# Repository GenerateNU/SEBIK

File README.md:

# SEBIK
The software portion of the safety subsystem will mostly deal with less critical errors as it is assumed that there is still communication between the microcontroller and its peripherals. The main software safety feature exists in the heating state. As the code runs through the state machine every 10 milliseconds or so, it checks if we must switch the band heater on or off based on two conditions. Are we at or above our optimal plastic melting temperature and have we heated at that optimal temperature for the full duration required to melt the pellets. 

Since, this is a software safety feature, there is a chance that it can fail in case we get stuck in some infinite loop due to an edge case or our microcontroller becomes unresponsive. A watchdog timer was used in the main state machine so it could reset the microcontroller in case any of these happened.

The band heater is allowed to operate for 4 minutes as some time is needed to reach the 165°C required to melt the PP. and 3.5 minutes is required for the band heater to completely melt all the PP within the barrel before moving to the next state. 

To do so, the code employs a timer that is initialized at the beginning of the Heating State. This conditional allows the heater to count the amount of time the band heater has been operating at the proper temperature. A watchdog timer will only run when the heater is at an optimal state and count until it reaches 4 minutes of heating time. In real time, this causes the process to run for longer than 4 minutes, however, this is necessary to ensure all the PP is melted.

## Directory Structure:
```
.
|
|───production  # contains files needed for final prototype
|   |
|   |───sebik-eCAD    # contains the KiCAD project
|   └───sebik-src     # contains the code needed for deployment
|
|───testing     # contains files relevant to testing components
|
└───README.md   # this file!
```

## Practice Good Git Hygiene!
1. Only commit files you intended to change
2. Create branches for each feature, and larger branches for each development effort (i.e. ```develop/*```)
3. Check your branch before starting work
4. Pull frequently to avoid conflicts
5. Make Pull Requests when you are ready to merge into a larger branch

## Git Resources

* [Setting up Git](https://fanatical-colossus-434.notion.site/Git-Installation-and-Setup-d07b7d1ab5544424876f9fd3b4a0b312)
* [Intro to Git Crash Course](https://fanatical-colossus-434.notion.site/Crash-Course-Intro-to-Git-809641611da9478b8f9cca8fd97e49fe)

## EE Resources

* [Intro to KiCAD](https://fanatical-colossus-434.notion.site/EE-Crashcourse-Using-Kicad-To-Design-Schematics-8c7091b07237425bae66616ad1f77371)
* [EE Crash Course](https://fanatical-colossus-434.notion.site/EE-Crash-Course-Hardware-2023-c0c7cd5b55cf401e87f8b6c2c8c84336)

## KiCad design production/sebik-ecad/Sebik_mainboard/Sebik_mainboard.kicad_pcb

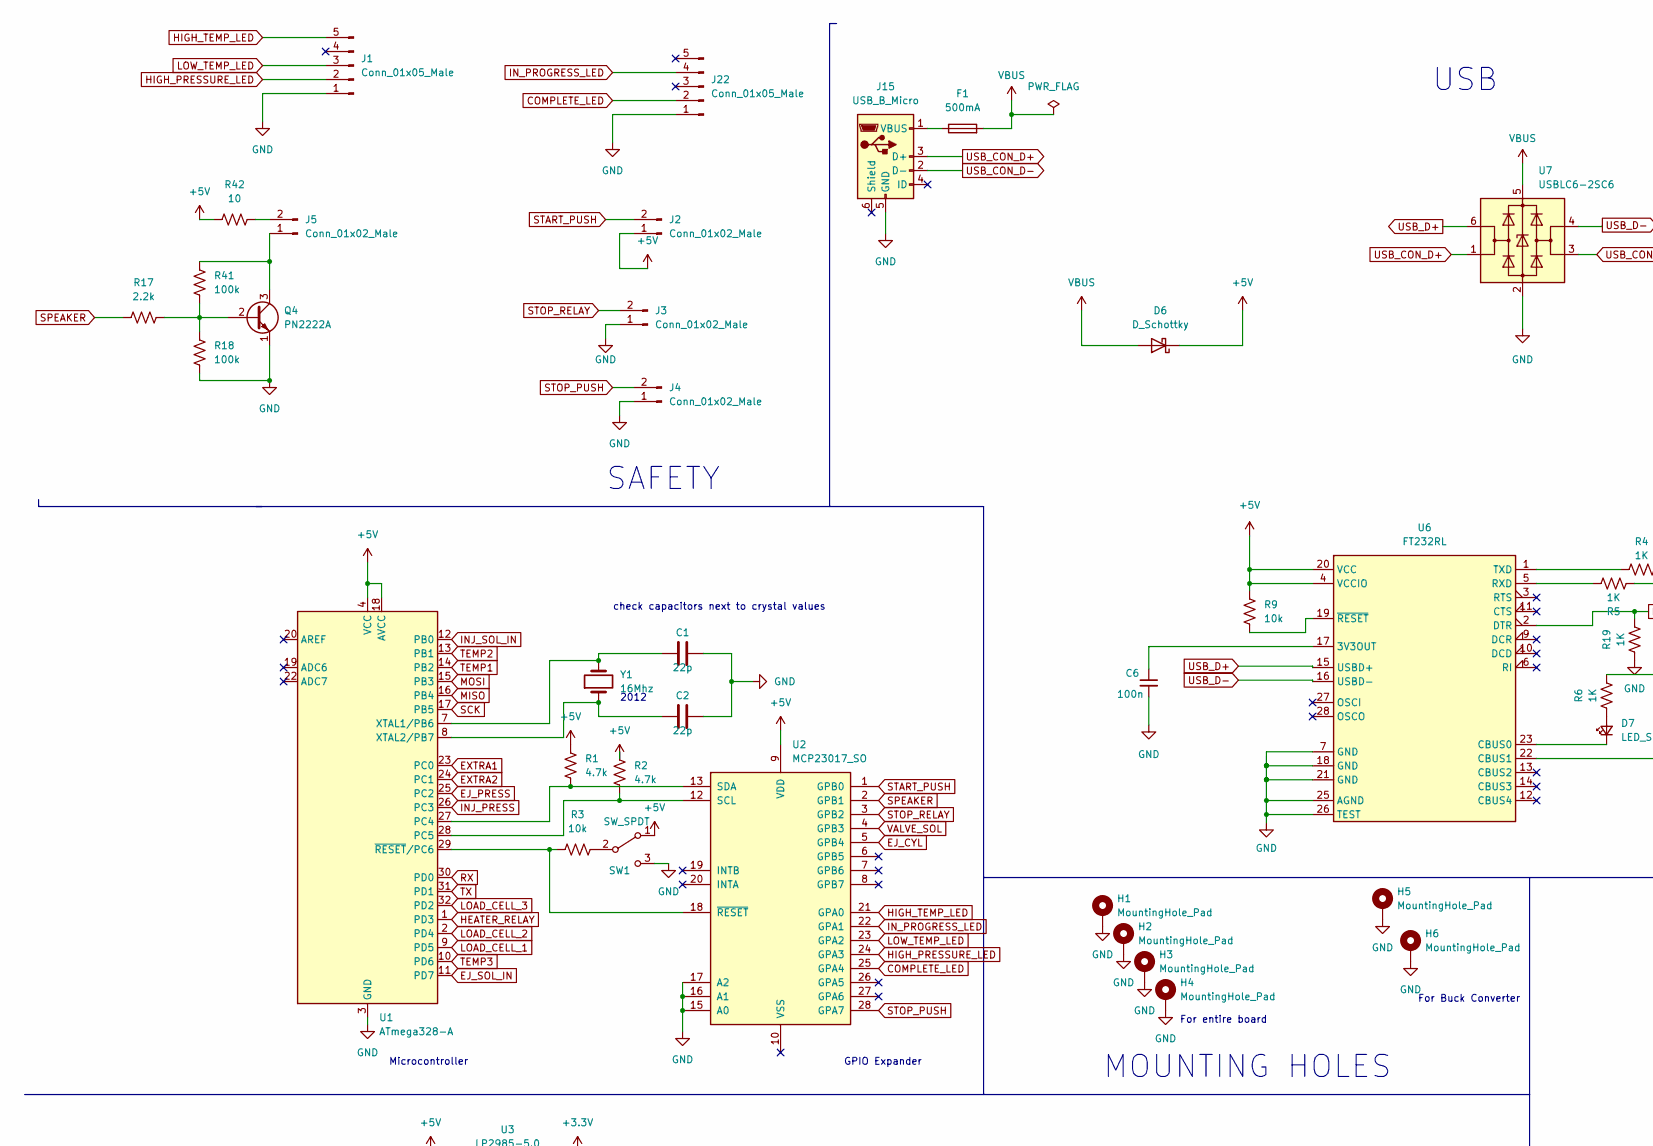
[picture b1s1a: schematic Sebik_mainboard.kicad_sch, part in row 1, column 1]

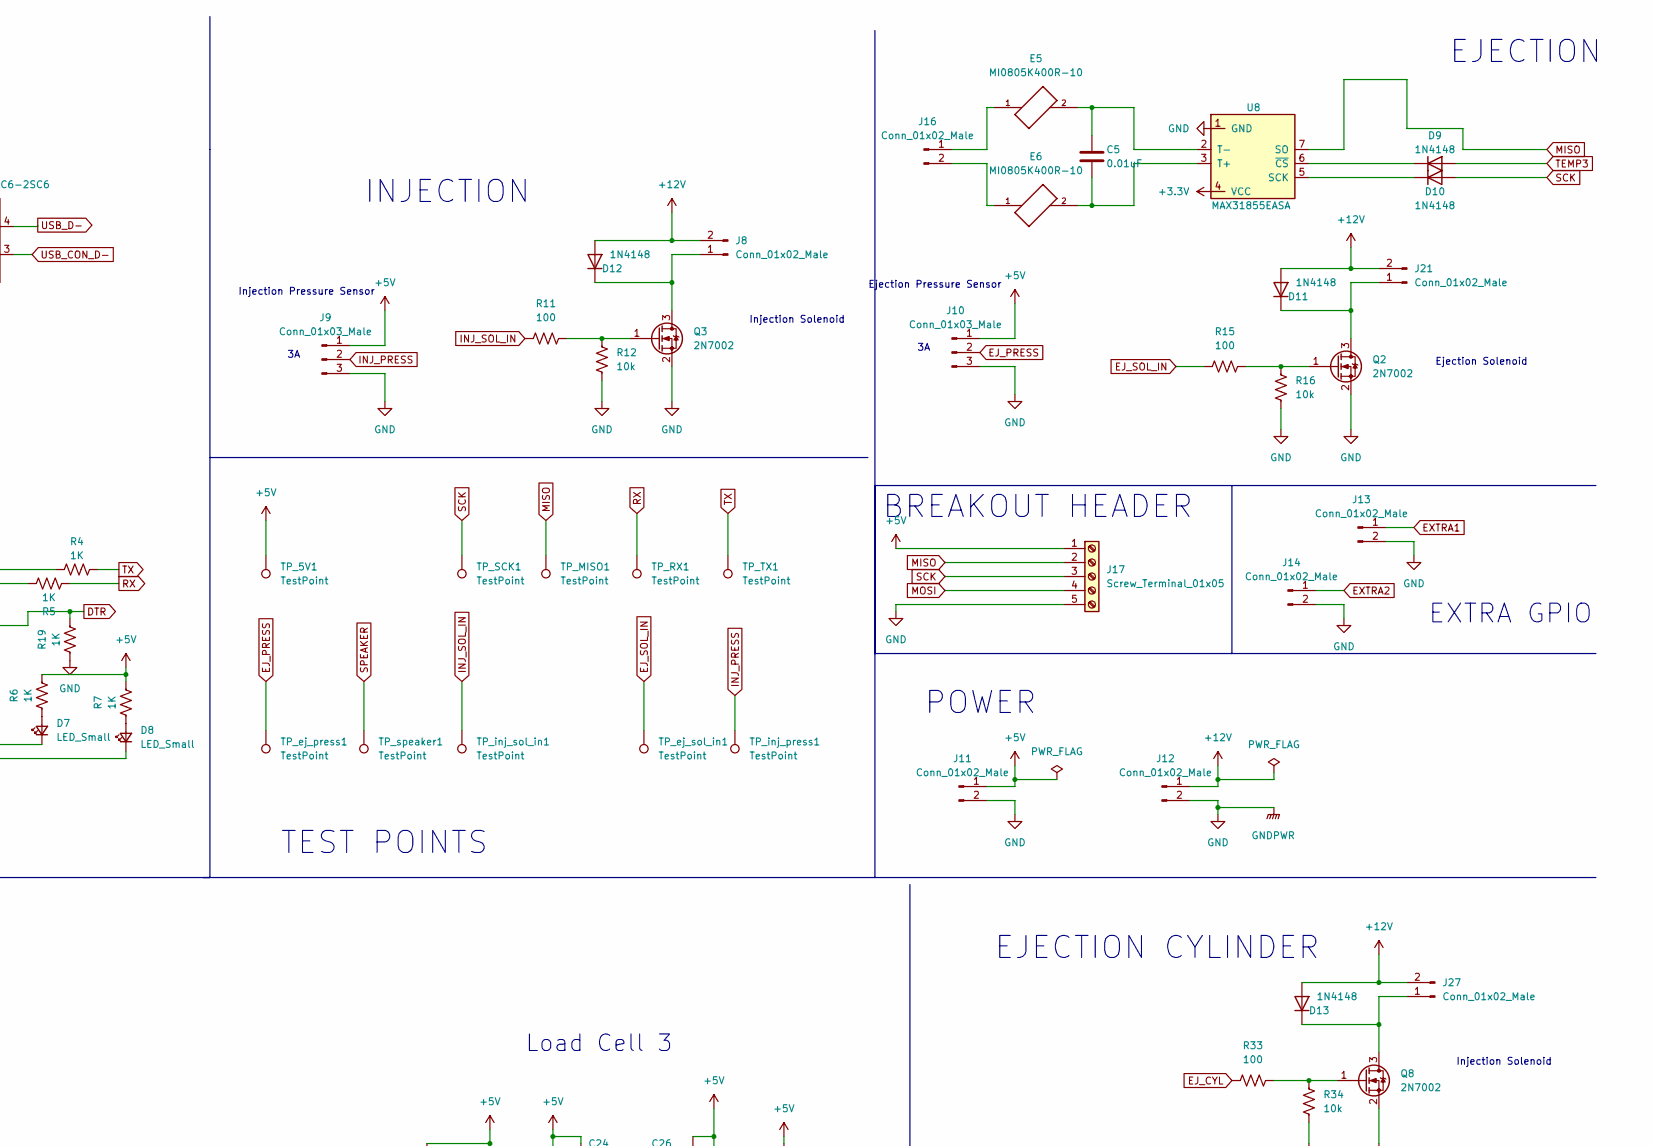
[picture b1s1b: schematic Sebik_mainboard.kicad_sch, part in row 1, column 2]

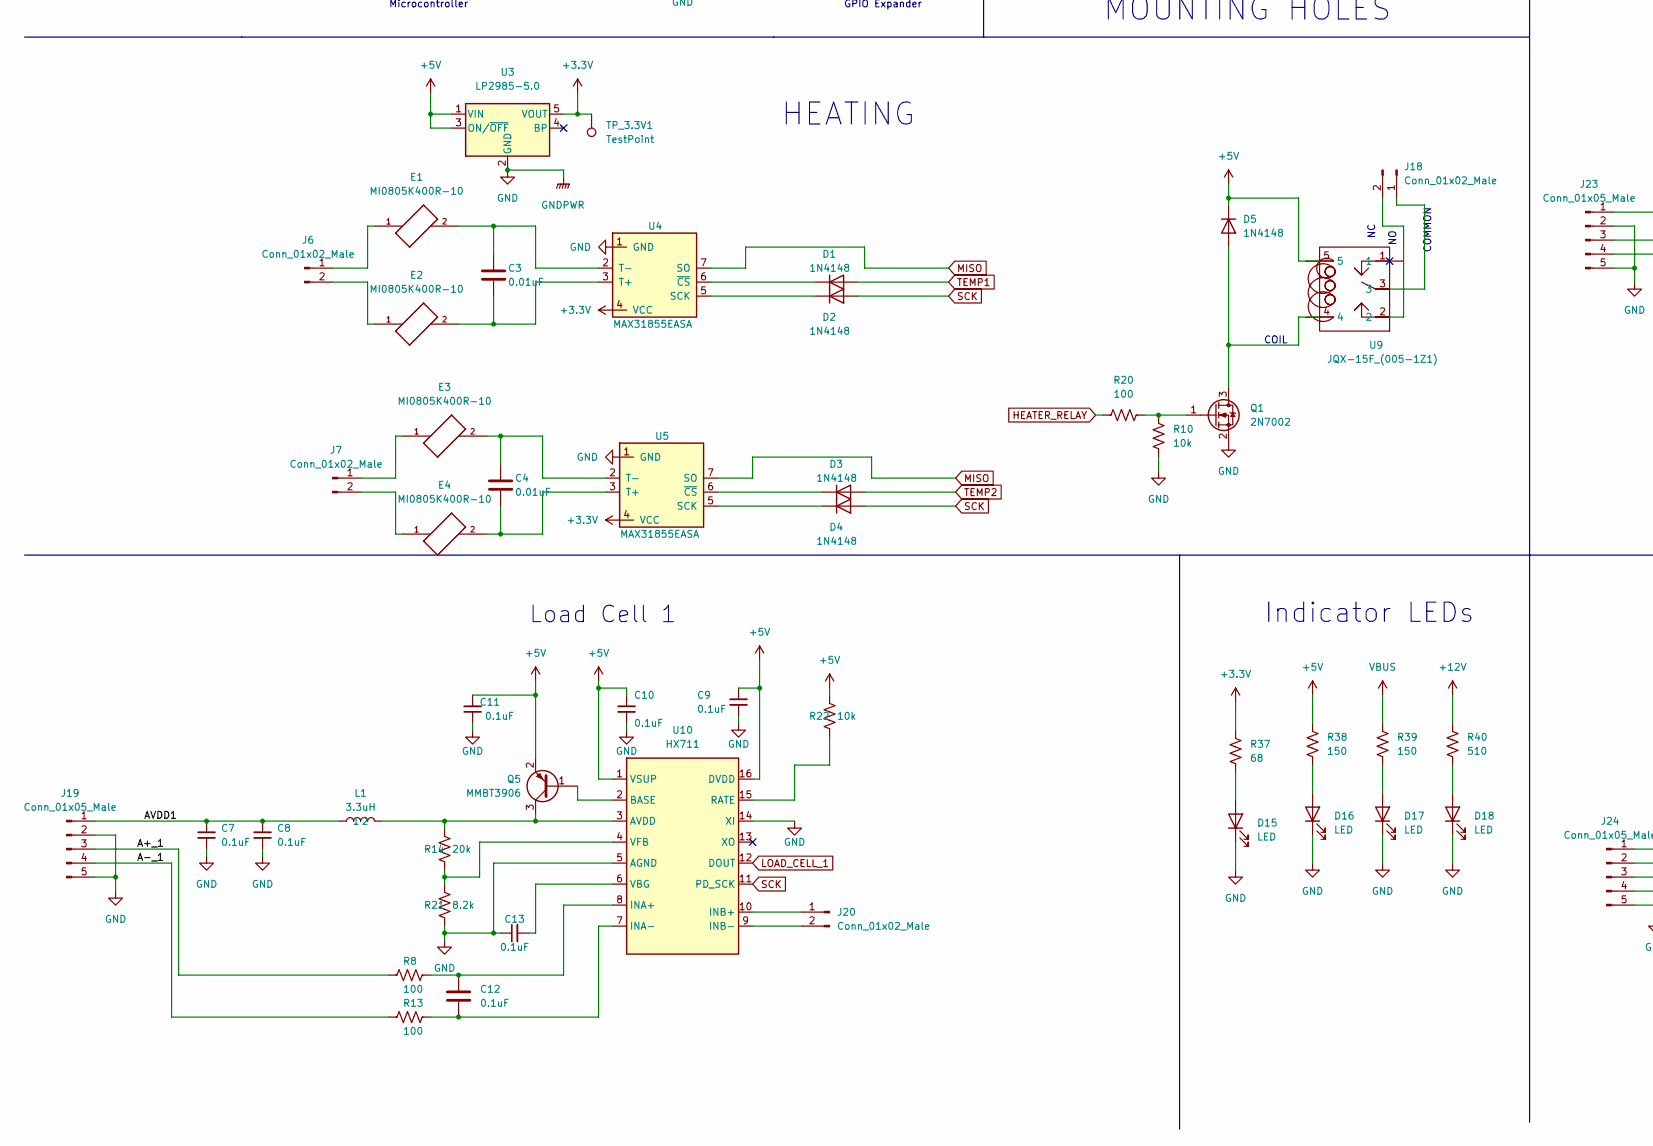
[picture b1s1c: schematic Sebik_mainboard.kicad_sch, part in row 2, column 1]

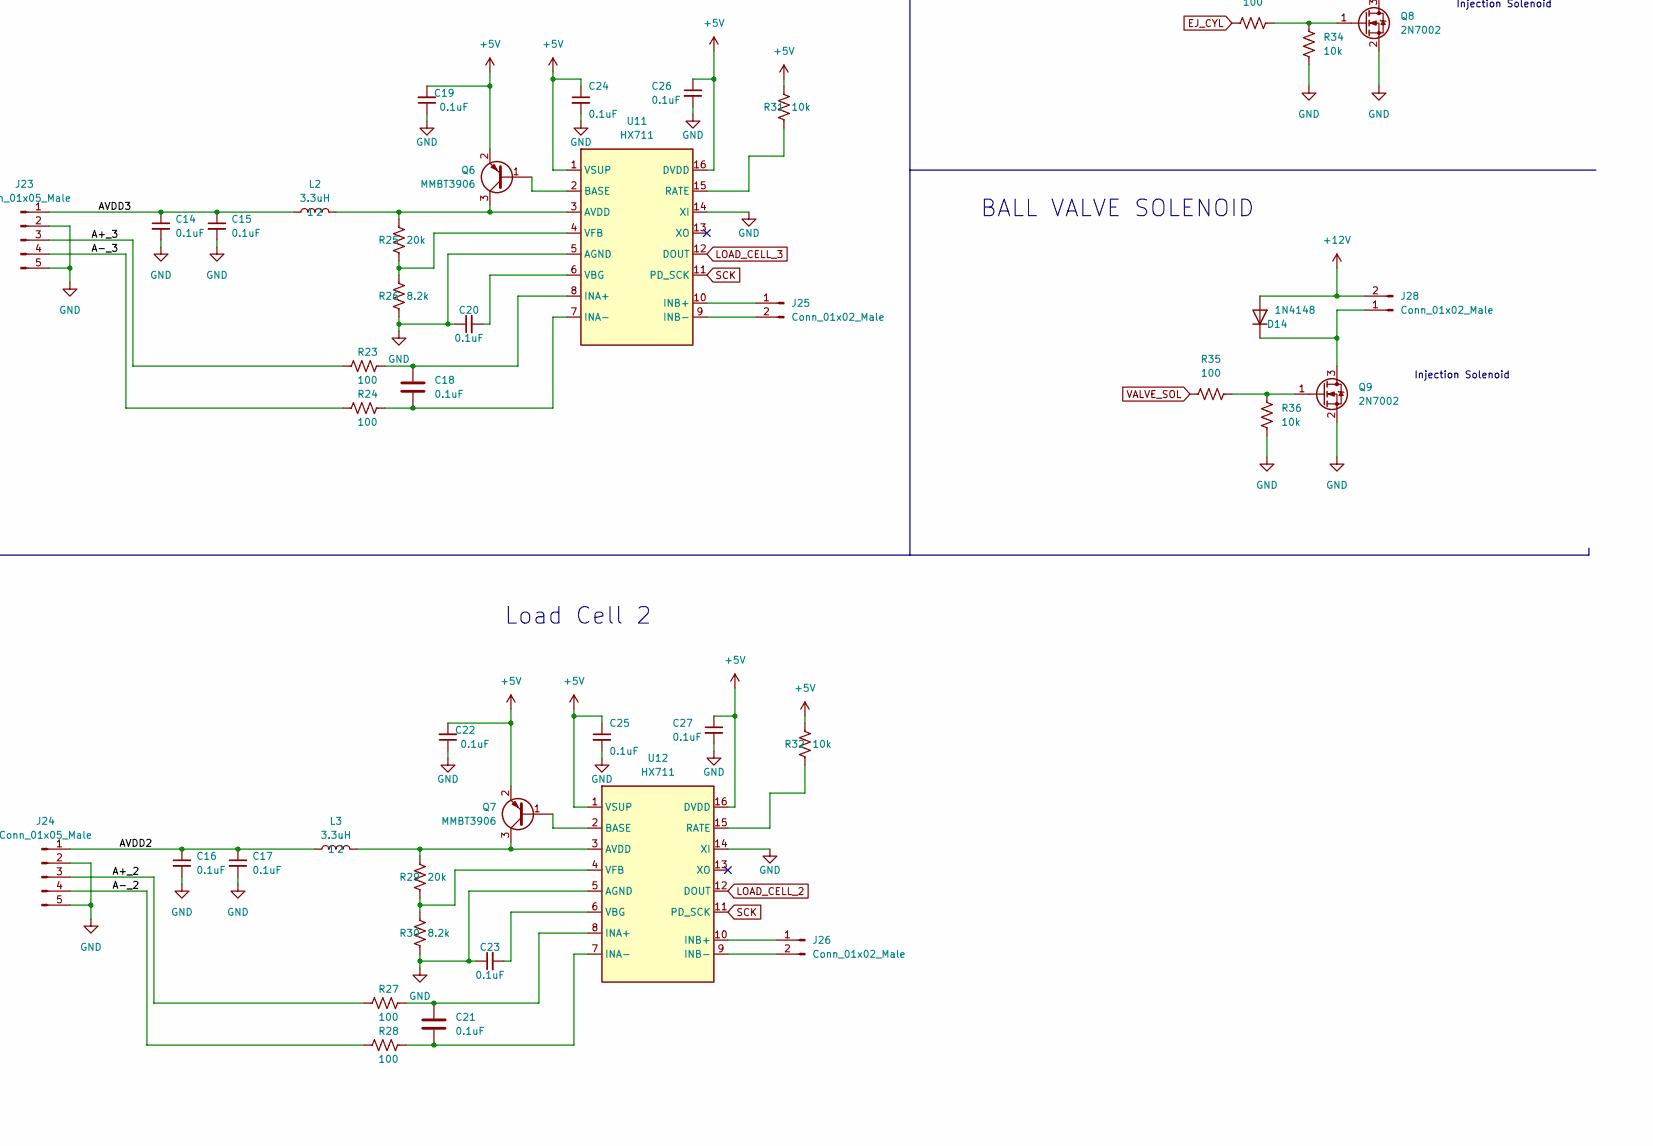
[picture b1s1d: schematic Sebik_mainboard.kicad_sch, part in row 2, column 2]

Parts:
C1, C2: 22p; C_0805_2012Metric
C3, C4, C5: 0.01uF; C_0805_2012Metric
C6: 100n; C_0805_2012Metric
C7, C8, C9, C10, C11, C12, C13, C14, C15, C16, C17, C18, C19, C20, C21, C22, C23, C24, C25, C26, C27: 0.1uF; C_0805_2012Metric
D1, D2, D3, D4, D5, D9, D10, D11, D12, D13, D14: 1N4148; D_0805_2012Metric
D6: D_Schottky; D_0805_2012Metric
D7, D8: LED_Small; LED_0805_2012Metric
D15, D16, D17, D18: LED; LED_0805_2012Metric
E1, E2, E3, E4, E5, E6: MI0805K400R-10; C_0805_2012Metric
F1: 500mA; Fuse_1210_3225Metric
H1, H2, H3, H4: MountingHole_Pad; MountingHole_3.2mm_M3_DIN965_Pad
H5, H6: MountingHole_Pad; MountingHole_2.2mm_M2_DIN965_Pad
J1, J22: Conn_01x05_Male; JST_XH_B5B-XH-A_1x05_P2.50mm_Vertical
J2, J3, J4, J5, J6, J7, J8, J11, J12, J13, J14, J16, J20, J21, J25, J26, J27, J28: Conn_01x02_Male; JST_XH_B2B-XH-AM_1x02_P2.50mm_Vertical
J9, J10: Conn_01x03_Male; JST_XH_B3B-XH-AM_1x03_P2.50mm_Vertical
J15: USB_B_Micro; USB_Micro-B_Amphenol_10103594-0001LF_Horizontal
J17: Screw_Terminal_01x05; PinHeader_1x05_P1.27mm_Vertical
J18: Conn_01x02_Male; JST_VH_B2P-VH-B_1x02_P3.96mm_Vertical
J19, J23, J24: Conn_01x05_Male; JST_XH_B5B-XH-AM_1x05_P2.50mm_Vertical
L1, L2, L3: 3.3uH; L_0805_2012Metric
Q1, Q2, Q3, Q8, Q9: 2N7002; SOT-23
Q4: PN2222A; TO-92_Inline
Q5, Q6, Q7: MMBT3906; SOT-23
R1, R2: 4.7k; R_0805_2012Metric
R3, R9, R10, R12, R16, R22, R31, R32, R34, R36: 10k; R_0805_2012Metric
R4, R5, R6, R7, R19: 1K; R_0805_2012Metric
R8, R11, R13, R15, R20, R23, R24, R27, R28, R33, R35: 100; R_0805_2012Metric
R14, R25, R29: 20k; R_0805_2012Metric
R17: 2.2k; R_0805_2012Metric
R18, R41: 100k; R_0805_2012Metric
R21, R26, R30: 8.2k; R_0805_2012Metric
R37: 68; R_0805_2012Metric
R38, R39: 150; R_0805_2012Metric
R40: 510; R_0805_2012Metric
R42: 10; R_0805_2012Metric
SW1: SW_SPDT; SW_SPDT_CK-JS102011SAQN
TP_3.3V1, TP_5V1: TestPoint; TestPoint_Pad_D1.5mm
TP_MISO1: TestPoint; TestPoint_Pad_D1.5mm
TP_RX1: TestPoint; TestPoint_Pad_D1.5mm
TP_SCK1: TestPoint; TestPoint_Pad_D1.5mm
TP_TX1: TestPoint; TestPoint_Pad_D1.5mm
TP_ej_press1: TestPoint; TestPoint_Pad_D1.5mm
TP_ej_sol_in1: TestPoint; TestPoint_Pad_D1.5mm
TP_inj_press1: TestPoint; TestPoint_Pad_D1.5mm
TP_inj_sol_in1: TestPoint; TestPoint_Pad_D1.5mm
TP_speaker1: TestPoint; TestPoint_Pad_D1.5mm
U1: ATmega328-A; TQFP-32_7x7mm_P0.8mm
U2: MCP23017_SO; SOIC-28W_7.5x17.9mm_P1.27mm
U3: LP2985-5.0; SOT-23-5
U4, U5, U8: MAX31855EASA; SOIC-8_3.9x4.9mm_P1.27mm
U6: FT232RL; SSOP-28_5.3x10.2mm_P0.65mm
U7: USBLC6-2SC6; SOT-23-6
U9: JQX-15F_(005-1Z1); JQX-15F(005-181) (1)
U10, U11, U12: HX711; SOP-16_3.9x9.9mm_P1.27mm
Y1: 16Mhz; Crystal_SMD_2520-4Pin_2.5x2.0mm

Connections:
+3.3V: R37.1, TP_3.3V1.1, U3.5 (VOUT), U4.4 (VCC), U5.4 (VCC), U8.4 (VCC)
+12V: D11.2 (A), D12.2 (A), D13.2 (A), D14.2 (A), J8.2, J12.1, J21.2, J27.2, J28.2, R40.1
/A+_1: J19.3, R8.2
/A+_2: J24.3, R27.2
/A+_3: J23.3, R23.2
/A-_1: J19.4, R13.2
/A-_2: J24.4, R28.2
/A-_3: J23.4, R24.2
/AVDD1: C7.1, C8.1, J19.1, L1.1
/AVDD2: C16.1, C17.1, J24.1, L3.1
/AVDD3: C14.1, C15.1, J23.1, L2.1
DTR: R19.2, U6.2 (DTR)
EJ_CYL: R33.2, U2.5 (GPB4)
EJ_PRESS: J10.2, TP_ej_press1.1, U1.25 (PC2)
EJ_SOL_IN: R15.1, TP_ej_sol_in1.1, U1.11 (PD7)
EXTRA1: J13.1, U1.23 (PC0)
EXTRA2: J14.1, U1.24 (PC1)
HEATER_RELAY: R20.1, U1.1 (PD3)
HIGH_PRESSURE_LED: J1.2, U2.24 (GPA3)
HIGH_TEMP_LED: J1.5, U2.21 (GPA0)
INJ_SOL_IN: R11.2, TP_inj_sol_in1.1, U1.12 (PB0)
IN_PROGRESS_LED: J22.4, U2.22 (GPA1); also elsewhere on the board
LOAD_CELL_1: U1.9 (PD5), U10.12 (DOUT)
LOAD_CELL_2: U1.2 (PD4), U12.12 (DOUT)
LOAD_CELL_3: U1.32 (PD2), U11.12 (DOUT)
LOW_TEMP_LED: J1.3, U2.23 (GPA2)
MISO: J17.2, TP_MISO1.1, U1.16 (PB4), U4.7 (SO), U5.7 (SO), U8.7 (SO)
MOSI: J17.4, U1.15 (PB3)
unnamed: C1.1, U1.7 (XTAL1/PB6), Y1.2
unnamed: C2.1, U1.8 (XTAL2/PB7), Y1.1
unnamed: C3.1, E1.2, U4.2 (T-)
unnamed: C3.2, E2.2, U4.3 (T+)
unnamed: C4.1, E3.2, U5.2 (T-)
unnamed: C4.2, E4.2, U5.3 (T+)
unnamed: C5.1, E5.2, U8.2 (T-)
unnamed: C5.2, E6.2, U8.3 (T+)
unnamed: C6.1, U6.17 (3V3OUT)
unnamed: C12.1, R8.1, U10.8 (INA+)
unnamed: C12.2, R13.1, U10.7 (INA-)
unnamed: C13.2, U10.6 (VBG)
unnamed: C18.1, R23.1, U11.8 (INA+)
unnamed: C18.2, R24.1, U11.7 (INA-)
unnamed: C20.2, U11.6 (VBG)
unnamed: C21.1, R27.1, U12.8 (INA+)
unnamed: C21.2, R28.1, U12.7 (INA-)
unnamed: C23.2, U12.6 (VBG)
unnamed: D1.1 (K), U4.6 (~CS)
unnamed: D2.1 (K), U4.5 (SCK)
unnamed: D3.1 (K), U5.6 (~CS)
unnamed: D4.1 (K), U5.5 (SCK)
unnamed: D5.2 (A), Q1.3 (D), U9.4
unnamed: D7.1 (K), U6.23 (CBUS0)
unnamed: D7.2 (A), R6.1
unnamed: D8.1 (K), U6.22 (CBUS1)
unnamed: D8.2 (A), R7.1
unnamed: D9.1 (K), U8.6 (~CS)
unnamed: D10.1 (K), U8.5 (SCK)
unnamed: D11.1 (K), J21.1, Q2.3 (D)
unnamed: D12.1 (K), J8.1, Q3.3 (D)
unnamed: D13.1 (K), J27.1, Q8.3 (D)
unnamed: D14.1 (K), J28.1, Q9.3 (D)
unnamed: D15.2 (A), R37.2
unnamed: D16.2 (A), R38.2
unnamed: D17.2 (A), R39.2
unnamed: D18.2 (A), R40.2
unnamed: E1.1, J6.1
unnamed: E2.1, J6.2
unnamed: E3.1, J7.1
unnamed: E4.1, J7.2
unnamed: E5.1, J16.1
unnamed: E6.1, J16.2
unnamed: F1.1, J15.1 (VBUS)
unnamed: J5.1, Q4.3 (C), R41.2
unnamed: J5.2, R42.2
unnamed: J18.1, U9.3
unnamed: J18.2, U9.2
unnamed: J20.1, U10.10 (INB+)
unnamed: J20.2, U10.9 (INB-)
unnamed: J25.1, U11.10 (INB+)
unnamed: J25.2, U11.9 (INB-)
unnamed: J26.1, U12.10 (INB+)
unnamed: J26.2, U12.9 (INB-)
unnamed: L1.2, Q5.3 (C), R14.1, U10.3 (AVDD)
unnamed: L2.2, Q6.3 (C), R25.1, U11.3 (AVDD)
unnamed: L3.2, Q7.3 (C), R29.1, U12.3 (AVDD)
unnamed: Q1.1 (G), R10.2, R20.2
unnamed: Q2.1 (G), R15.2, R16.2
unnamed: Q3.1 (G), R11.1, R12.2
unnamed: Q4.2 (B), R17.2, R18.2, R41.1
unnamed: Q5.1 (B), U10.2 (BASE)
unnamed: Q6.1 (B), U11.2 (BASE)
unnamed: Q7.1 (B), U12.2 (BASE)
unnamed: Q8.1 (G), R33.1, R34.2
unnamed: Q9.1 (G), R35.1, R36.2
unnamed: R1.2, U1.27 (PC4), U2.13 (SDA)
unnamed: R2.2, U1.28 (PC5), U2.12 (SCL)
unnamed: R3.1, SW1.2 (B)
unnamed: R3.2, U1.29 (~RESET/PC6), U2.18 (~RESET)
unnamed: R4.2, U6.1 (TXD)
unnamed: R5.2, U6.5 (RXD)
unnamed: R9.1, U6.19 (~RESET)
unnamed: R14.2, R21.1, U10.4 (VFB)
unnamed: R22.2, U10.15 (RATE)
unnamed: R25.2, R26.1, U11.4 (VFB)
unnamed: R29.2, R30.1, U12.4 (VFB)
unnamed: R31.2, U11.15 (RATE)
unnamed: R32.2, U12.15 (RATE)
RX: R5.1, TP_RX1.1, U1.30 (PD0)
SCK: D2.2 (A), D4.2 (A), D10.2 (A), J17.3, TP_SCK1.1, U1.17 (PB5), U10.11 (PD_SCK), U11.11 (PD_SCK), U12.11 (PD_SCK)
SPEAKER: R17.1, TP_speaker1.1, U2.2 (GPB1)
START_PUSH: J2.2, U2.1 (GPB0)
STOP_PUSH: J4.2, U2.28 (GPA7)
STOP_RELAY: J3.2, U2.3 (GPB2)
TEMP1: D1.2 (A), U1.14 (PB2)
TEMP2: D3.2 (A), U1.13 (PB1)
TEMP3: D9.2 (A), U1.10 (PD6)
TX: R4.1, TP_TX1.1, U1.31 (PD1)
USB_CON_D+: J15.3 (D+), U7.1 (I/O1)
USB_CON_D-: J15.2 (D-), U7.3 (I/O2)
USB_D+: U6.15 (USBD+), U7.6 (I/O1)
USB_D-: U6.16 (USBD-), U7.4 (I/O2)
VALVE_SOL: R35.2, U2.4 (GPB3)
VBUS: D6.2 (A), F1.2, R39.1, U7.5 (VBUS)

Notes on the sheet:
Injection Solenoid
check capacitors next to crystal values
BREAKOUT HEADER
MOUNTING HOLES
EXTRA GPIO
For Buck Converter
For entire board
Indicator LEDs
COIL
HEATING
POWER
Load Cell 2
BALL VALVE SOLENOID
Injection Pressure Sensor
Load Cell 3
2012
EJECTION CYLINDER
GPIO Expander
EJECTION
TEST POINTS
Microcontroller
Ejection Solenoid
SAFETY
USB
COMMON
Ejection Pressure Sensor
INJECTION
Load Cell 1

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
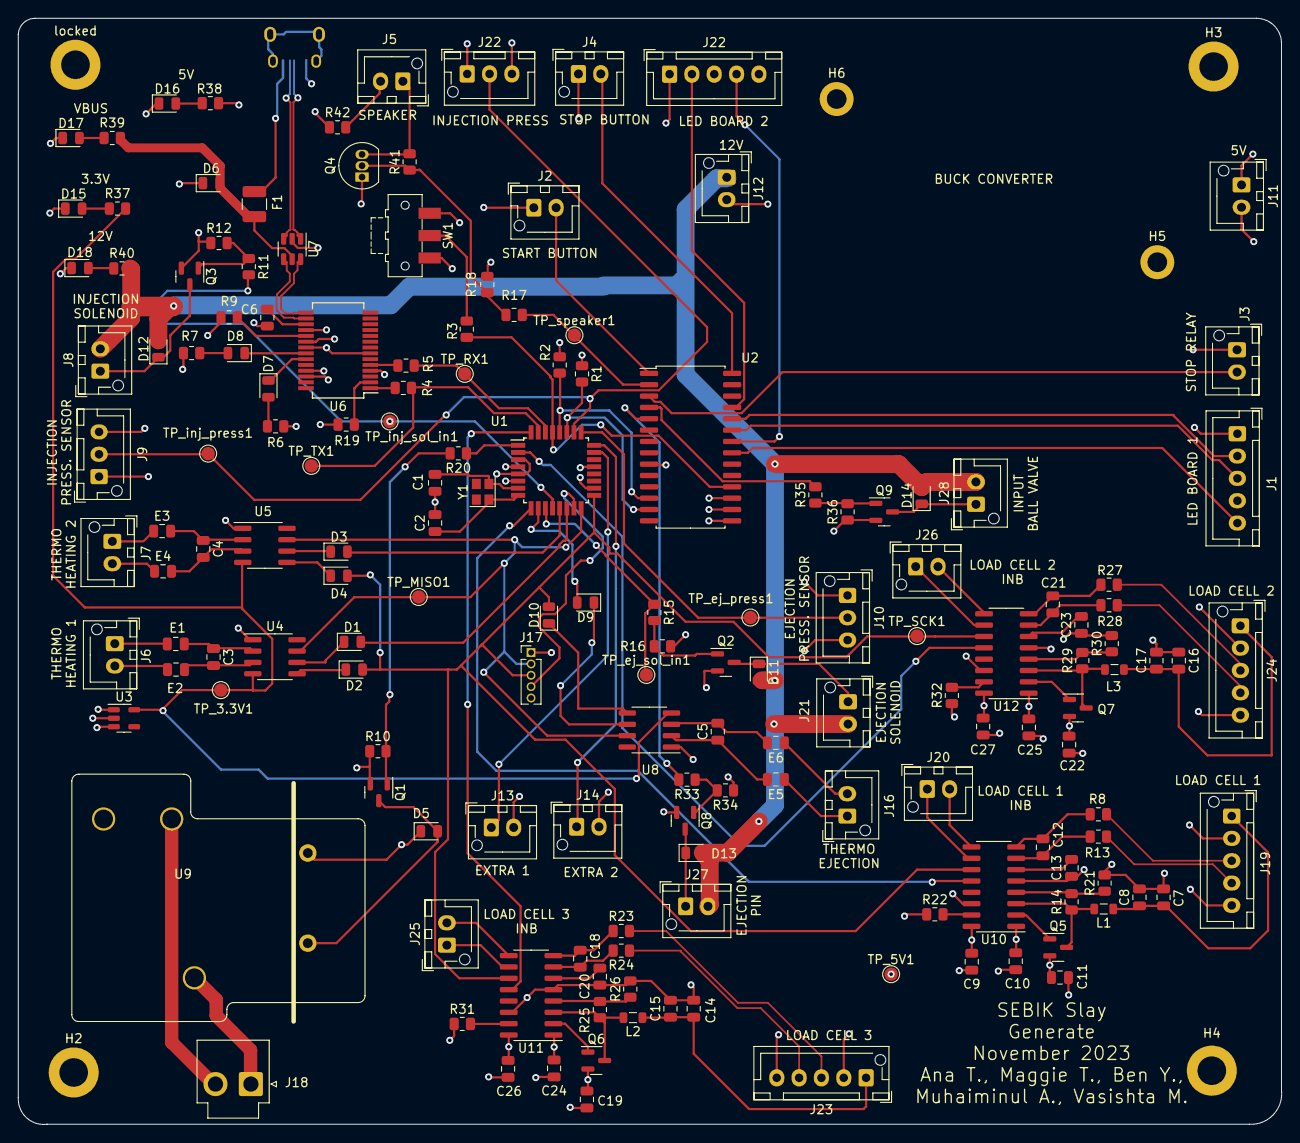
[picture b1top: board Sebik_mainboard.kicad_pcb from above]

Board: 4 copper layers, 141.4 x 123.8 mm, 166 parts (1 on the bottom side), 127 nets.

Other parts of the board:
J22#2: Conn_01x05_Male; JST_XH_B5B-XH-A_1x05_P2.50mm_Vertical
locked: MountingHole_Pad; MountingHole_3.2mm_M3_DIN965_Pad

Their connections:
IN_PROGRESS_LED: J22#2.4; also elsewhere on the board

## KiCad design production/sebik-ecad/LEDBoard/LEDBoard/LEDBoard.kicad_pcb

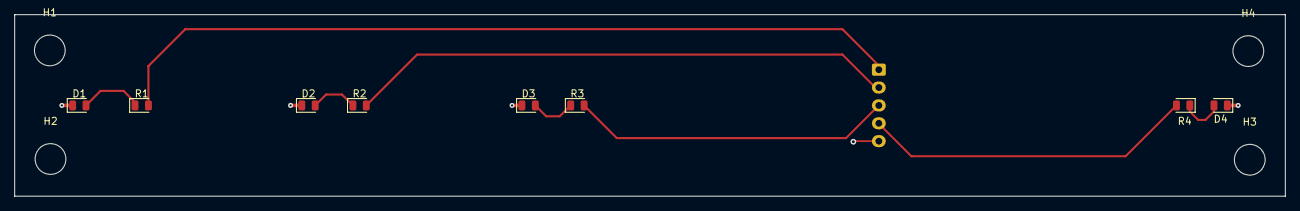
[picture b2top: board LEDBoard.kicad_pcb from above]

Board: 2 copper layers, 177.8 x 25.4 mm, 13 parts (1 on the bottom side), 9 nets.

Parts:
D1, D2, D3, D4: LED; LED_0805_2012Metric
H1, H2, H3, H4: MountingHole_Pad; MountingHole_4.3mm_M4
J1: Conn_01x05_Male; JST_XH_B5B-XH-A_1x05_P2.50mm_Vertical
R1, R2, R3, R4: 250; LED_0805_2012Metric

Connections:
GND: D1.1 (K), D2.1 (K), D3.1 (K), D4.1 (K), J1.5
High Pressure/Complete Yellow LED: J1.4, R4.2
High Temp Yellow LED: J1.1, R1.2
In Progress Yellow LED: J1.2, R2.2
Low Temp Yellow LED: J1.3, R3.2
unnamed: D1.2 (A), R1.1
unnamed: D2.2 (A), R2.1
unnamed: D3.2 (A), R3.1
unnamed: D4.2 (A), R4.1

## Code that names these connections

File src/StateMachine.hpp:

#ifndef STATEMACHINE_HPP
#define STATEMACHINE_HPP

#include <HX711_ADC.h>
#include <Adafruit_MCP23X17.h>
#include <Adafruit_MAX31855.h>

// UI pins
#define START_PUSHBUTTON_E 1
#define SPEAKER_E 2
#define HIGH_TEMP_LED_E 21
#define IN_PROGRESS_LED_E 22
#define LOW_TEMP_LED_E 23
#define HIGH_PRESSURE_LED_E 24
#define COMPLETE_LED_E 25
//#define HARD_STOP_BUTTON_E 7

// Solenoid pins
#define INJECTION_SOLENOID 12
#define EJECTION_SOLENOID 11
#define BALL_VALVE_SOLENOID_E 4
#define EJECTION_CYLINDER_SOLENOID_E 5

// SPI
#define MISO 16
#define MOSI 15
#define SCK 17

// Sensor pins
#define TEMP_SENSOR1 14
#define TEMP_SENSOR2 13
#define TEMP_SENSOR3 10
#define INJECTION_SENSOR 26
#define EJECTION_SENSOR 25
#define LOAD_CELL_SENSOR1 9
#define LOAD_CELL_SENSOR2 2
#define LOAD_CELL_SENSOR3 32

// Relays
#define HEATER_RELAY 1
#define AIR_PUMP_RELAY 23 // Used to be EXTRA1

#define EXTRA2 24

const int HIGH_TEMP_IN_CELSIUS = 175;
const int OPTIMAL_TEMP_IN_CELSIUS = 165;

const int SAFE_TEMP_TO_TOUCH_IN_CELSIUS = 40;

const int HIGH_PRESSURE_IN_PSI = 100;
const int OPTIMAL_PRESSURE_IN_PSI = 90; 
const int LOW_PRESSURE_IN_PSI = 80;

const float PETRI_DISH_WEIGHT = 100; // g, change this later to actual weight

const float calibration_factor = 199900; //-7050 worked for my 440lb max scale setup

enum States
{
    START,
    CLAMPING,
    PLASTIC_DISPENSES,
    HEATING,
    INJECTING,
    EJECTING,
    FINSHED,
    HARD_STOP
};

class StateMachineHandler
{
    private:
        enum States m_currentState;
        int m_timeHeated = 0; 
        float m_plastic_dispensed = 0;
        float m_previous_weight;
        Adafruit_MCP23X17 gpioExpander;

    public:
        StateMachineHandler(Adafruit_MCP23X17 expander);

        ~StateMachineHandler();

        void InitializePins();

        void StartStateMachine();

        // Updates the current state
        void Update(States state);

        // Triggers state machine

        // Main state machine
        void MainStateMachine();

        // Executes start procedure
        void Start();

        // Executes clamping procedure
        void Clamping();

        // Executes the plastic dispensing procedure
        void PlasticDispense();

        // Gets the current hopper weight
        float GetTotalHopperWeight();

        // Executes the heating procedure
        void Heating();

        // Executes the injecting procedure
        void Injecting();

        // Executes the unclamping procedure
        void Unclamping();

        // Executes the finish procedure
        void Finish();

        // Gets the pressure reading from the supplied pressure sensor pin
        float GetPressureReading(int pin);

        // Gets the temperature reading from the supplied thermocouple
        double GetTempReading(Adafruit_MAX31855 thermocouple);

        // Returns if the plastic in the ejection drawer is safe to touch
        bool IsPlasticSafeToTouch();

        void HardwareTest();

        bool IsStartButtonPressed();

        void PlaySpeaker();

        void HighTempLEDOn();
        
        void HighTempLEDOff();

        void LowTempLEDOn();

        void LowTempLEDOff();

        void HighPressureLEDOn();

        void HighPressureLEDOff();

        void InProgressLEDOn();

        void InProgressLEDOff();

        void CompleteLEDOn();

        void CompleteLEDOff();

        bool IsPressureHandled(int pin);
};

#endif

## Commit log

2023-09-08 Initializing all directories
2023-10-18 Committing the current file for main schematic and PCB and LED board schematic and PCB
2023-10-19 updated schematic with usb port, test points, and mounting holes
2023-10-19 added non power net test points, numbered all parts and added crystal and switch footprints
2023-10-23 added mounting holes for buck converter and connector for 5v from buck
2023-10-23 added connector for relay to shut down power
2023-10-23 changed microUSB to USBC
2023-10-23 took off pulldown resistors on thermocouple sensors
2023-10-24 LED Board edits
2023-10-24 Addressed comments from Nick
2023-10-24 added project name
2023-11-01 Create Code
2023-11-02 platform Io file
2023-11-08 Shit ton of changes idk
2023-11-08 Forgot to add these
2023-11-08 Last one i promise
2023-11-08 Last last one
2023-11-12 adding last version of PCB- sent to fabrication
2023-11-12 Updates for matching pins, watchdog timer, testing hardware
2023-11-14 Code cleanup
2023-11-14 Updated Injection Method
2023-11-16 Low Pressure Error Handling
2023-11-16 code for thermocouple sensor and band heater to connect
2023-11-17 Completed Injection Code v1
2023-11-17 kept working on the code
2023-11-17 Just changed member variable name
2023-11-17 Stuff
2023-11-19 nomanclature
2023-11-19 Heating changes added.
2023-11-19 Heating changes 0.2
2023-11-19 Heating changes 0.3:
2023-11-21 Updated Pressure Sensor Code
2023-11-21 Start and stop stuff
2023-11-21 Plastic dispense 11/20
2023-11-21 whateevr
2023-11-27 A bunch of shit
2023-11-29 Major major changes
2023-11-29 Code cleannup
2023-12-08 Final code
